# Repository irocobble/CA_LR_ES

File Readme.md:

# Acoustic Sensing Node

**Team:** Aninda Majumdar ([@irocobble](https://github.com/irocobble)) · Subham Basak · Kartik Kajra

A **two-board, field-deployable acoustic sensor** for search-and-rescue. The node
is placed in rubble or debris and listens for signs of a trapped person (voice,
tapping, banging). It works out **which direction** the sound came from and
sends a GPS-tagged alert over LoRa to a rescue dashboard.

Searching collapsed structures is a race against time, and the hardest question
is *where to dig*. Instead of sending people onto unstable rubble to listen, the
node sends the ears in first.

<p align="center">
  
  &nbsp;
  
  <br>
  <em>Left: Board 1, the 8-mic array (2-layer, Ø100 mm). Right: Board 2, the main board (4-layer, 50 × 75 mm).</em>
</p>

---

## Contents

1. [How it works](#how-it-works)
2. [Architecture](#architecture)
3. [Why two boards](#why-two-boards)
4. [Hardware](#hardware)
5. [Microphone array](#microphone-array)
6. [Board-to-board interface](#board-to-board-interface)
7. [Power](#power)
8. [Signal processing on the K210](#signal-processing-on-the-k210)
9. [Voice detection model](#voice-detection-model)
10. [Host software and dashboard](#host-software-and-dashboard)
11. [Prototype results](#prototype-results)
12. [Project status](#project-status)
13. [Open items](#open-items)
14. [Repository layout](#repository-layout)
15. [Getting started](#getting-started)
16. [Engineering notes](#engineering-notes)
17. [Roadmap](#roadmap)
18. [References](#references)

---

## How it works

```
 sound ──▶ 8 MEMS mics ──▶ K210 ──────────────────────────▶ ESP32 ──▶ LoRa ──▶ rescue dashboard
                           │ 1. capture all channels,          │ adds GPS position,
                           │    sampled on the same clock      │ IMU data, timestamp
                           │ 2. "is this a human voice?"       │
                           │ 3. "which direction?"             │
                           └─ sends only the result ───────────┘
                              (angle, confidence, voice yes/no)
```

1. **Listen.** Eight digital microphones sit on a 90 mm circle. They all run
   off one shared clock, so the tiny arrival-time differences between them are
   real and measurable.
2. **Decide.** A small voice-detection model running on the K210 decides
   continuously whether the sound looks like a human voice.
3. **Locate.** The K210 compares the signals from opposite microphones
   (GCC-PHAT) to find the arrival-time difference, then turns it into a bearing.
4. **Report.** Only the result (angle, confidence, level, voice flag) goes to the
   ESP32. No raw audio crosses between the boards.

The K210 stays **powered and listening all the time**. It is not duty-cycled.

---

## Architecture

The system is split across **two boards** that solder together along an 11-pin
castellated edge.

| Board | Layers | Size | Carries |
|---|---|---|---|
| **Board 1: Mic array** | 2 | Ø100 mm | 8× INMP441, Kendryte K210 (Sipeed M1), 12 V→5 V and 12 V→3V3 regulators |
| **Board 2: Main** | 4 | 50 × 75 mm | ESP32 (QFN-48), SX1262 LoRa, MAX-M10S GNSS, MPU-9250 IMU, USB-C hub + 2× USB-UART, 12 V→3V3 regulator |

| Processor | Role |
|---|---|
| **Kendryte K210** (Sipeed M1) | Everything acoustic: I2S master for the array, voice detection, direction finding |
| **ESP32** (QFN-48, 5 × 5 mm) | System host: LoRa, GNSS, IMU, USB, alert formatting |

**Why the K210?** A single K210 I2S peripheral has **four data inputs driven by
one clock generator**. With two microphones per data line, that is eight
channels sampled on exactly the same clock edges. Direction finding depends
entirely on that, and the K210 provides it with nothing to synchronise. It also
has a hardware FFT unit and an audio processor (APU) that can do beamforming,
which we plan to evaluate later.

```
                 ┌──────────────────────────────────────────┐
                 │  BOARD 1: Mic array  (2-layer, Ø100 mm)  │
   8× INMP441 ───┤                                          │
   circle,       │  I2S: 4 data lines, 1 shared clock       │
   r = 45 mm     │            ↓                             │
                 │  K210 / Sipeed M1  (always on)           │
                 │   · voice detection (3-feature model)    │
                 │   · direction of arrival (GCC-PHAT)      │
                 └───────────────┬──────────────────────────┘
                                 │  11-pin castellated edge
                                 │  12 V · mic clock · 2× UART · boot/reset
                 ┌───────────────┴──────────────────────────┐
                 │  BOARD 2: Main  (4-layer, 50 × 75 mm)    │
                 │  ESP32 ── SX1262 LoRa      → U.FL        │
                 │        ── MAX-M10S GNSS    → U.FL        │
                 │        ── MPU-9250 IMU                   │
                 │        ── Wi-Fi/BLE        → U.FL        │
                 │  USB-C → CH334F hub → 2× CP2102N         │
                 └──────────────────────────────────────────┘
```

The IMU is there on purpose. Tapping on rubble produces both a sound and a
vibration. Requiring both reduces false alarms in a way an acoustic-only system
cannot.

---

## Why two boards

The two halves of the design have **opposite needs**:

| | Mic array | Main electronics |
|---|---|---|
| What sets the size | **Physics**: the mics must be far apart to measure direction | **Density**: as small as routing allows |
| Area | Ø100 mm (≈ 7,850 mm²) | 50 × 75 mm (3,750 mm²) |
| Signals | Slow I2S lines, no RF | 3 RF paths, USB, fine-pitch parts |
| Layers needed | **2** | **4** |

On a single board, the whole area would have to be 4-layer, because the LoRa,
GNSS and Wi-Fi antenna feeds need a solid ground plane and 50 Ω traces. We
would be paying 4-layer prices for a large area whose only job is holding
microphones 45 mm from the centre.

### Real cost (as ordered)

Both boards were ordered from **Robu.in**. Prices include shipping.

| Board | Layers | Area | Price paid | Price per mm² |
|---|---|---|---|---|
| Board 1: Mic array | 2 | ≈ 7,850 mm² | **₹900** | ≈ ₹0.115 |
| Board 2: Main | 4 | 3,750 mm² | **₹1,800** | ≈ ₹0.48 |
| **Total (split design)** | | | **₹2,700** | |

On our order, **4-layer cost ≈ 4.2× more per mm² than 2-layer.**

What a single 4-layer board would have cost, at the same ₹0.48/mm²:

| Single-board option | Area | Estimated price | Saving from splitting |
|---|---|---|---|
| Ø100 mm round (smallest that holds the array) | ≈ 7,850 mm² | ≈ ₹3,770 | ≈ 28% |
| 100 × 100 mm (more realistic once both boards' parts fit) | 10,000 mm² | ≈ ₹4,800 | ≈ 44% |

**The split saves roughly 28–44% on bare PCBs.** This is an estimate: fabs have
minimum charges and quantity tiers, so price is not exactly proportional to area.
It is still a fair comparison because both quotes came from the same supplier.

Benefits that do not show up on the invoice:

- **Cheap iteration.** The array geometry is the least certain part of the
  design. Changing it means a new 2-layer board, not a new 4-layer one.
- **Contained failure.** A damaged mic board does not scrap the main board.
- **Assembly yield.** The finest-pitch parts (ESP32 QFN-48 at 0.35 mm,
  2× QFN-28, QFN-24) are all on the small board.
- **RF kept away from audio.** The three antennas are physically separated from
  the microphone traces.

**The trade-off:** the castellated joint is a new failure point and cannot be
probed once soldered. That is why only slow signals cross it: no RF, no
high-speed bus.

---

## Hardware

### Board 1: Mic array (`Board1_2layers/Mic+MPU/`)

| Function | Device | Ref |
|---|---|---|
| Acoustic processor | Sipeed M1 (Kendryte K210) | U12 |
| Microphones | 8× INMP441 I2S MEMS | U1–U6, U15, U16 |
| Buck 12 V → 5 V (K210) | AP63205WU | U14 |
| Buck 12 V → 3V3 (mics) | AP63203WU | U10 |
| Power input | JST-XH 2-pin, polarised | J1 |
| Board interface | 11-pin castellated, 3.2 mm pitch | J3 |
| Buttons | Boot, Reset | SW4, SW3 |

> The `Mic+MPU` folder name is historical. The MPU-9250 is on Board 2.

<p align="center">
  
  &nbsp;
  
  <br><em>Board 1, top and bottom. The microphone sound holes are on the bottom face.</em>
</p>

<p align="center">
  
  <br><em>Board 1 layout in KiCad.</em>
</p>

### Board 2: Main (`board2_4layers/`)

| Function | Device | Ref |
|---|---|---|
| Host MCU | ESP32 (QFN-48, 5 × 5 mm) | U7 |
| External SPI flash | SPI NOR, SOIC-8 | U6 |
| LoRa transceiver | SX1262 module | U1 |
| GNSS receiver | u-blox MAX-M10S | U3 |
| IMU | MPU-9250 (9-axis) | U4 |
| USB hub | CH334F | CH334F1 |
| USB-UART bridges (ESP32 + K210) | 2× CP2102N | U8, U9 |
| USB ESD protection | USBLC6-4SC6 | U2 |
| Buck 12 V → 3V3 | AP63203WU | U5 |
| Antennas | 3× U.FL: LoRa, GNSS, Wi-Fi | J2, J4, J5 |
| USB connector | USB Type-C | J1 |
| Crystals | 40 MHz (ESP32), 12 MHz (hub) | Y2, Y1 |
| Buttons | EN, BOOT | SW1, SW2 |

Stack-up: GND on F.Cu, In1.Cu and B.Cu; +3V3 on In2.Cu.

<p align="center">
  
  &nbsp;
  
  <br><em>Board 2, top and bottom.</em>
</p>

<p align="center">
  
  <br><em>Board 2 layout in KiCad.</em>
</p>

---

## Microphone array

Eight INMP441 digital microphones on a circle of **radius 45.00 mm**, spaced
45° apart. Each one is rotated to face the centre, so every microphone has the
same trace shape back to the K210.

Two microphones share each data line. The INMP441's `L/R` pin decides which
half of the stereo frame each one uses: one takes the left slot, the other the
right.

| Data line | K210 pin | Mics | Angles |
|---|---|---|---|
| `SD_1` | IO20 | U1, U2 | 90°, 45° |
| `SD_2` | IO21 | U5, U6 | 0°, 315° |
| `SD_3` | IO22 | U15, U16 | 270°, 225° |
| `SD_4` | IO23 | U3, U4 | 180°, 135° |
| `SCK_MIC` | IO18 | shared bit clock | |
| `WS` | IO19 | shared word select | |

All eight sample on the same bit clock, so every channel is **phase-coherent**.
This is exactly what direction finding needs, and it is why digital MEMS mics
were chosen over analog mics behind a multiplexed ADC.

Every K210 IO used has a **200 Ω series resistor and an ESD diode**, as Sipeed
requires for the M1 module.

> **Sound enters from the bottom.** Each mic sits over a 1.05 mm hole through
> the PCB, so the openings in the enclosure must be on the bottom face.

**Geometry numbers:**

| Quantity | Value | Why it matters |
|---|---|---|
| Adjacent mic spacing | 2r·sin(22.5°) = 34.4 mm | Spatial aliasing above c / (2 × 0.0344) ≈ **5.0 kHz** |
| Opposite mic spacing | 90 mm | Longest baseline, best angle resolution |
| Max arrival-time difference | 90 mm / 343 m/s ≈ 262 µs | Only ≈ **4.2 samples** at 16 kHz, so sub-sample timing is required |

> **About IO20.** On the Sipeed **Maix development board**, IO20 is wired to the
> board's own onboard microphone, so it cannot be used for an external mic there.
> On our PCB the bare **M1 module** is used, which has no onboard microphone, so
> IO20 is free. This only matters if you test the firmware on a Maix board.

---

## Board-to-board interface

11 positions, 3.2 mm pitch, castellated. Board 2 solders directly onto Board 1,
with no connector and no cable.

| Pin | Net | Direction | Purpose |
|---|---|---|---|
| 1 | `+12V` | → Board 2 | Unregulated; each board regulates locally |
| 2 | `SCK_MIC` | K210 → ESP32 | Mic bit clock |
| 3 | `WS` | K210 → ESP32 | Mic word select |
| 4 | `SD1` | mics → ESP32 | Lets the ESP32 hear one mic pair (spare / diagnostics) |
| 5 | `UART_TX` | ESP32 → K210 | Commands |
| 6 | `UART_RX` | K210 → ESP32 | Results: voice flag, confidence, bearing |
| 7 | `RX` | K210 → CP2102N | K210 programming, transmit |
| 8 | `TX` | CP2102N → K210 | K210 programming, receive |
| 9 | `Boot` | CP2102N → K210 | IO16 boot-mode select |
| 10 | `RST` | CP2102N → K210 | Reset (1.8 V domain) |
| 11 | `GND` | | Return |

`TX` and `RX` on pins 7–8 are named **from the USB bridge's point of view** on
both boards.

Pins 2–4 were originally intended for a low-power wake detector on the ESP32.
Since the K210 now stays on all the time, that wake path is not needed. The
pins stay as a spare way for the ESP32 to listen to one mic pair. If used, the
ESP32 must be an I2S **slave**, because the K210 drives the clock.

**No raw audio crosses the joint in normal operation.** The mics feed the K210
directly; the UART carries only results.

---

## Power

```
12 V in (JST-XH, polarised)
   │
   ├── Board 1 ── AP63205 ──▶ +5V   → Sipeed M1 (K210)
   │           └─ AP63203 ──▶ +3V3  → 8× INMP441
   │
   └── via J3 pin 1 ──▶ Board 2 ── AP63203 ──▶ +3V3
                                     → ESP32, SX1262, MAX-M10S, MPU-9250, flash
```

Only 12 V and GND cross the joint, so no regulated rail loses voltage across it
and the RF and audio sections do not share regulator noise.

**Estimated ≈ 3.3 W total (≈ 320 mA at 12 V)**, mostly the K210 (≈ 1.5 W).
This is an estimate and will be measured once the boards are assembled.

---

## Signal processing on the K210

The firmware is plain C on the **kendryte-standalone-sdk**, in two CMake projects:

| Project | Build flag | Output | Use |
|---|---|---|---|
| Recorder | `-DPROJ=Recorder` | `Recorder.bin` | Streams raw mic audio to the PC for datasets and calibration |
| Detector | `-DPROJ=Detector` | `Detector.bin` | Runs voice detection and direction finding on the chip |

### Capture

- 16 kHz nominal. The K210's PLL gives a real rate of about **15,986 Hz**. The
  difference is small and does not affect the results.
- Samples are 32-bit from the INMP441, shifted down to 16-bit
  (`SAMPLE_SHIFT = 13`, the smallest shift where no channel clips).
- The conversion to 16-bit **saturates** instead of wrapping. A wrapped sample
  looks like a loose wire, which is very confusing during debugging.
- A **100 Hz high-pass filter** (4th-order Butterworth) removes rumble and DC
  before anything else.

### Direction of arrival (GCC-PHAT)

For each pair of opposite microphones:

1. Take a **1024-point FFT (64 ms)** of both channels.
2. Compute the cross-spectrum and divide each bin by its own magnitude
   (the **PHAT** weighting). This keeps only phase, which is what carries timing.
3. **Keep only 300–3400 Hz** (the speech band). Without this mask, the empty
   bins are amplified to the same weight as real ones and the answer is
   essentially random. Measured: a true delay of 1.50 samples was estimated as
   0.14 unmasked and 1.49 masked.
4. **Search for the delay directly at fractional lags.** A coarse pass in
   0.10-sample steps, then a fine pass in 0.01-sample steps around the best one.
   Each lag is evaluated with the FFT shift theorem, so no curve-fitting is
   needed. This matters because the whole array spans only about 4 samples of
   delay; whole-sample steps would give very coarse bearings.
5. The search range comes from the spacing:
   `max lag = spacing / c × fs × 1.4` (40% extra for echoes and measurement error).
6. Two perpendicular pairs give `lag_x` and `lag_y`, and the bearing is
   `atan2(lag_y, lag_x)`.
7. Results are rejected if the sound is too quiet (`-45 dB` level gate), the
   correlation is too weak (`< 0.08`), or the delay is impossibly large.

Direction finding runs on **any loud enough sound**, not only on speech. The
voice flag is reported alongside it.

**Calibration matters.** On the prototype, two I2S channels start on different
word-select edges, which adds a constant offset between them. We measured
`lag_x` bias = **−0.93** and `lag_y` bias = **+0.95** samples, and the firmware
subtracts them (`DOA_LAG_X_BIAS`, `DOA_LAG_Y_BIAS`).

### What the array can and cannot do

- It reports **one bearing per update**: the dominant sound source. Separating
  several people talking at once needs a much larger array (roughly 0.5 m or
  more across), which is not practical for a node this size.
- It gives **direction, not distance**. On the dashboard, how far a dot is from
  the centre shows **how old** the detection is, not how far away the source is.
- Distance comes from **combining several nodes** (triangulation), which is on
  the roadmap.

### Result packet (K210 → host)

20 bytes, sent at `REPORT_HZ = 20`:

```
[5A A6] [len=0x10] [seq] [angle×10 : i16] [conf×1000 : u16] [score×100 : i16]
[level_db×10 : i16] [speech : u8] [warm : u8] [lag_x×100 : i16] [lag_y×100 : i16] [xor] [pad]
```

Raw-audio frames from the Recorder use:

```
[5A A5] [seq : u8] [blk : u16] [nch : u8] [int16 samples × blk·nch] [sum16]
```

The sequence number lets the PC detect and count dropped bytes. Before framing,
one lost byte silently turned the rest of a recording into noise while the WAV
file still looked valid.

---

## Voice detection model

A **logistic regression on 3 hand-picked features**, small enough to run on the
K210 as a single dot product.

| Feature | What it measures |
|---|---|
| `harmonicity` | Strength of the pitch peak in the autocorrelation (human pitch range, lags 40–266 samples) |
| `voice_band_ratio` | Share of energy in 300–3400 Hz (512-point Hann-window FFTs) |
| `snr_db` | Level above a rolling noise floor (20th percentile over the last 8 s) |

- Trained in Python (`Accoustic_Sensing_Node/ML/`). The feature scaler is folded into the weights and
  exported as `vad3_model.h`, so the chip does no extra scaling.
- Decision threshold (logit) **2.389**, then smoothed over **3** consecutive
  decisions (`VAD_SMOOTH_K = 3`).
- `FEATURE_VERSION = 4`. The firmware and Python feature code must match. The
  version number makes a mismatch obvious.
- Evaluation uses **grouped cross-validation by recording file**, so clips from
  the same recording never appear in both training and test. The main metric is
  **recall at 5% false-positive rate**, because false alarms are what make
  rescuers stop trusting a sensor.

### Dataset status

Our own recordings (`INMP_441_Dataset/`) are combined with public datasets
(`Public_Dataset/`). Every file goes through a quality check (dropped bytes,
clipping, DC offset, rumble, SNR) before it is used.

We also run a **confound check**: a classifier trained only on the *background*
of each recording, with the speech removed. If it can still tell the classes
apart, the model could be learning *which session* a clip came from instead of
*whether someone is speaking*.

| Dataset version | Background-only AUC | Target |
|---|---|---|
| First dataset | 0.905 – 0.94 | < 0.65 |
| Latest | **0.812** | < 0.65 |

It is improving, but still above target. Recording speech and non-speech
**interleaved in the same session, room and distance** is the fix in progress.

---

## Host software and dashboard

Python tools on the PC, all reachable from one entry point:

```
python capstone.py --help
```

| Command | What it does |
|---|---|
| `status`, `devices`, `linktest`, `inspect` | Check setup, list serial ports, test the link, inspect captures |
| `record` | Record labelled clips from the board |
| `qc`, `filters` | Dataset quality check, filter tests |
| `train`, `train-corpus`, `export` | Train the model and export `vad3_model.h` |
| `predict` | Run the model on WAV files |
| `serve`, `monitor`, `gui` | Live API + dashboard, console monitor, desktop GUI (`sar_gui.py`) |

**API server** (`api_server.py`): reads the K210's result packets from serial
and serves them over HTTP on all interfaces (port 8000 by default), so a phone
on the same Wi-Fi hotspot can open the dashboard.

| Endpoint | Returns |
|---|---|
| `/api/detections` | Detections from the last 15 s |
| `/api/state` | Latest bearing, level, voice flag |
| `/api/threshold` | Read or change the detection threshold |
| `/api/health` | Server and serial-link status |
| `/` | `dashboard.html`, the radial display |

It uses a threaded server with HTTP/1.1 keep-alive, which fixed the lag we saw
on phones over a hotspot.

<p align="center">
  
  <br><em>Live dashboard in the browser.</em>
</p>

---

## Prototype results

Before the PCBs, the full pipeline was built on a breadboard: a Sipeed Maix
board with **4 INMP441 mics in a 40 mm square**. Opposite corners are paired, so
the baseline is the square's diagonal, **56.6 mm**.

<!-- Add the photo later: save it as Accoustic_Sensing_Node/images/prototype_breadboard.jpg and delete these comment markers
<p align="center">
  
  <br><em>Breadboard prototype: Maix board + 4 INMP441 in a 40 mm square.</em>
</p>
-->

What works on the prototype:

- Phase-coherent 4-channel capture on one I2S peripheral
- On-chip voice detection and GCC-PHAT bearing, streamed live to the dashboard
- North and West bearings accurate before calibration; East and South were
  tilted until the cross-channel bias correction was added

**A measured accuracy table (true angle vs reported angle, several distances)
will be added once the PCB is assembled.** Numbers from the breadboard are not
representative of the final board, so they are not published here.

---

## Project status

### Hardware

- [x] Board 1 schematic and layout complete; 8 mics at exact geometry (r = 45.000 mm)
- [x] Board 1: K210 power, programming, boot/reset, 1.8 V reset domain; 200 Ω + ESD on every IO
- [x] Board 2 schematic and layout complete, DRC clean
- [x] Board 2: ESP32 core, LoRa, GNSS (active-antenna bias-T), IMU, USB-C hub with auto boot/reset for both processors
- [x] **Both boards ordered** (Robu.in)
- [ ] Assembly and bring-up
- [ ] Measured power consumption

### Firmware (K210)

- [x] `Recorder` and `Detector` CMake projects
- [x] Framed, checksummed audio stream with sequence numbers
- [x] On-chip 3-feature voice detector (`vad3_model.h`, `FEATURE_VERSION = 4`)
- [x] Working 4-mic GCC-PHAT direction finding on the prototype, with bias calibration
- [ ] 8-channel capture on the new array
- [ ] Re-measure all DOA constants on the circular array
- [ ] Evaluate the K210 APU hardware beamformer

### Firmware (ESP32)

- [ ] LoRa, GNSS and IMU drivers
- [ ] UART link to the K210 and alert formatting
- [ ] Sound + vibration fusion

### Host software

- [x] `capstone.py` single entry point, `sar_gui.py` desktop GUI
- [x] API server + dashboard, 15 s detection window, keep-alive
- [x] Dataset QC, training, grouped evaluation, C-header export
- [ ] Multi-node triangulation view

---

## Open items

| # | Item | Where | What to do |
|---|---|---|---|
| 1 | **DOA constants are for the 4-mic breadboard** | Firmware | `DOA_SPACING_MM`, `SAMPLE_SHIFT` and both lag biases must be re-measured on the circular array (opposite pair = 90 mm) |
| 2 | **Every opposite pair spans two data lines** | Firmware | e.g. 0° is on `SD_2` and 180° on `SD_4`. Each data line may have its own timing offset, so calibrate a **per-data-line offset** at bring-up (the prototype needed ≈ ±0.9 samples) |
| 3 | **Channel order is not ring order** | Firmware | K210 inputs D0–D3 = `SD_4`, `SD_3`, `SD_2`, `SD_1`. Build the channel→angle table and confirm it with a tap test at each mic |
| 4 | Dataset confound | ML | Background-only AUC 0.812, target < 0.65. Record both classes interleaved in the same session |
| 5 | Measured DOA accuracy table | Testing | After PCB assembly |
| 6 | Flash part name | Board 2 | U6 value field shows `AT25SF081`; update it to the part actually fitted |
| 7 | CP2102N no-connect pins | Board 2 | Add no-connect flags on U8/U9 pin 10 (cosmetic, clean ERC) |
| 8 | Stale BOM export | Board 2 | `Accoustic_Sensing_Node.csv` is from an older revision; re-export from KiCad |
| 9 | Battery operation | Both | Node runs from 12 V only; battery + boost planned |
| 10 | One M2.5 mounting hole per board | Both | Add more before the enclosure is fixed |
| 11 | Enclosure | Mechanical | Sound openings on the bottom face, antenna clearance, survives drops |

---

## Repository layout

Everything for the acoustic node lives in the `Accoustic_Sensing_Node/` folder:

```text
Accoustic_Sensing_Node/
├── README.md                     ← copy of this file
├── images/                       ← all pictures used in this README
│
├── Board1_2layers/
│   ├── Mic+MPU/                  KiCad project: mic array board (2-layer)
│   │   ├── Mic.pretty/           INMP441 footprint (with sound hole)
│   │   ├── Connectors.pretty/    11-pin castellated footprint
│   │   └── output/               Gerbers as ordered
│   └── mic/INMP441.kicad_mod
│
├── board2_4layers/               KiCad project: main board (4-layer)
│   ├── *.pretty/                 custom footprints (LoRa, GNSS, USB hub, edge pads)
│   └── Output/                   Gerbers + drill as ordered
│
├── Recording_Via_IOT_Devices/
│   ├── firmware/
│   │   ├── K210/src/Recorder/    raw multi-channel streaming
│   │   ├── K210/src/Detector/    main_detector.c, sar_features.c, sar_doa.c, vad3_model.h
│   │   └── esp32_1mic/           single-mic ESP32 recorder (dataset collection)
│   ├── record.py, devices.py     recorder and per-board serial settings
│   ├── api_server.py             HTTP API + serial reader
│   ├── dashboard.html            radial live display
│   ├── detector_monitor.py       console monitor
│   └── link_test.py              serial link test
│
├── ML/                           features, training, QC, export to C header
├── capstone.py                   single entry point for all tools
├── sar_gui.py                    desktop GUI
├── requirements.txt
├── run_gui.bat, build_exe.bat
└── BUILD.md                      building the firmware and the .exe
```

Datasets (`INMP_441_Dataset/`, `Public_Dataset/`) are **not** stored in the repo
because of their size.

---

## Getting started

Run everything from inside the acoustic folder:

```bash
cd Accoustic_Sensing_Node
```

### 1. Python tools

```bash
pip install -r requirements.txt
python capstone.py status
```

Try the dashboard with no hardware:

```bash
python Recording_Via_IOT_Devices/api_server.py --demo
# open http://localhost:8000
```

### 2. Build and flash the K210 firmware

```bash
cd Recording_Via_IOT_Devices/firmware/K210
mkdir build && cd build
cmake .. -DPROJ=Detector -DTOOLCHAIN=/opt/kendryte-toolchain/bin
make
kflash -p COM12 -b 1500000 Detector.bin
```

> **Delete the `build/` folder when switching between `Recorder` and
> `Detector`.** CMake caches the project name, so otherwise it silently builds
> the old one again.

See `BUILD.md` for Windows details.

### 3. Run live

```bash
python Recording_Via_IOT_Devices/api_server.py --port COM12
# optional: --capture session.bin  (save the raw stream to replay later)
#           --wav heard.wav        (save what the detector is hearing)
#           --replay session.bin   (replay a saved session, no hardware)
```

Then open `http://<pc-ip>:8000` on any device on the same network.

---

## Engineering notes

Things learned the hard way, kept here so they are not learned twice:

- **Measure, don't assume.** Every DOA constant on the prototype came from
  measurement, not a datasheet. Mic spacing is measured between the actual
  sound holes, in **millimetres**.
- **Serial port settings.** pyserial asserts DTR and RTS by default. That
  resets the ESP32 and puts the K210 into its bootloader, where it sends
  nothing. `devices.py` clears both before opening the port.
- **UART pins.** The ESP32 transmits on GPIO5, so the K210 uses **IO31 as RX and
  IO30 as TX**.
- **ESP32 GPIO12 stays unconnected.** It sets the flash voltage at reset; high
  selects 1.8 V.
- **K210 IO voltages.** IO0–IO35 are 3.3 V, IO36–IO47 are 1.8 V. Every signal
  used is IO35 or below.
- **ESP32 flash mode.** Start in DIO; QIO needs chip-specific setup.
- **Faulty mics happen.** During prototyping one INMP441 was dead and one had
  a blocked sound hole (≈ 6.6 dB quieter). Check every channel's level before
  trusting a bearing.

---

## Roadmap

- Assemble both boards; bring up 8-channel capture
- Re-calibrate DOA on the circular array and publish a measured accuracy table
- Compare the K210 APU hardware beamformer with software GCC-PHAT
- Move the voice model to the 8-mic front end
- ESP32: LoRa, GNSS, IMU and the end-to-end alert path
- Combine sound and vibration (IMU) to reduce false alarms
- Multi-node triangulation on the dashboard
- Battery power (the K210 stays always on, so battery size is set by its ≈ 1.5 W)
- Enclosure: sound openings, antenna clearance, drop survival

---

## Applications

**Main use:** search-and-rescue: locating people trapped under collapsed
buildings. Several nodes across a site turn a large, uncertain search area into
a short list of places worth digging.

**Other uses:** perimeter and intrusion detection, wildlife monitoring, noise
source mapping, remote sensor networks with human-presence detection.

---

## References

- C. Knapp and G. Carter, *The Generalized Correlation Method for Estimation of
  Time Delay*, IEEE Trans. ASSP, 1976 (GCC-PHAT)
- J. DiBiase, *A High-Accuracy, Low-Latency Technique for Talker Localization
  in Reverberant Environments Using Microphone Arrays*, PhD thesis, Brown
  University, 2000 (SRP-PHAT)
- Sipeed M1 datasheet: module pinout, IO voltages, reset constraints
- Kendryte K210 datasheet and kendryte-standalone-sdk
- InvenSense INMP441 datasheet
- Espressif *ESP32 Hardware Design Guidelines*

---

## License

Under active development. License to be decided.

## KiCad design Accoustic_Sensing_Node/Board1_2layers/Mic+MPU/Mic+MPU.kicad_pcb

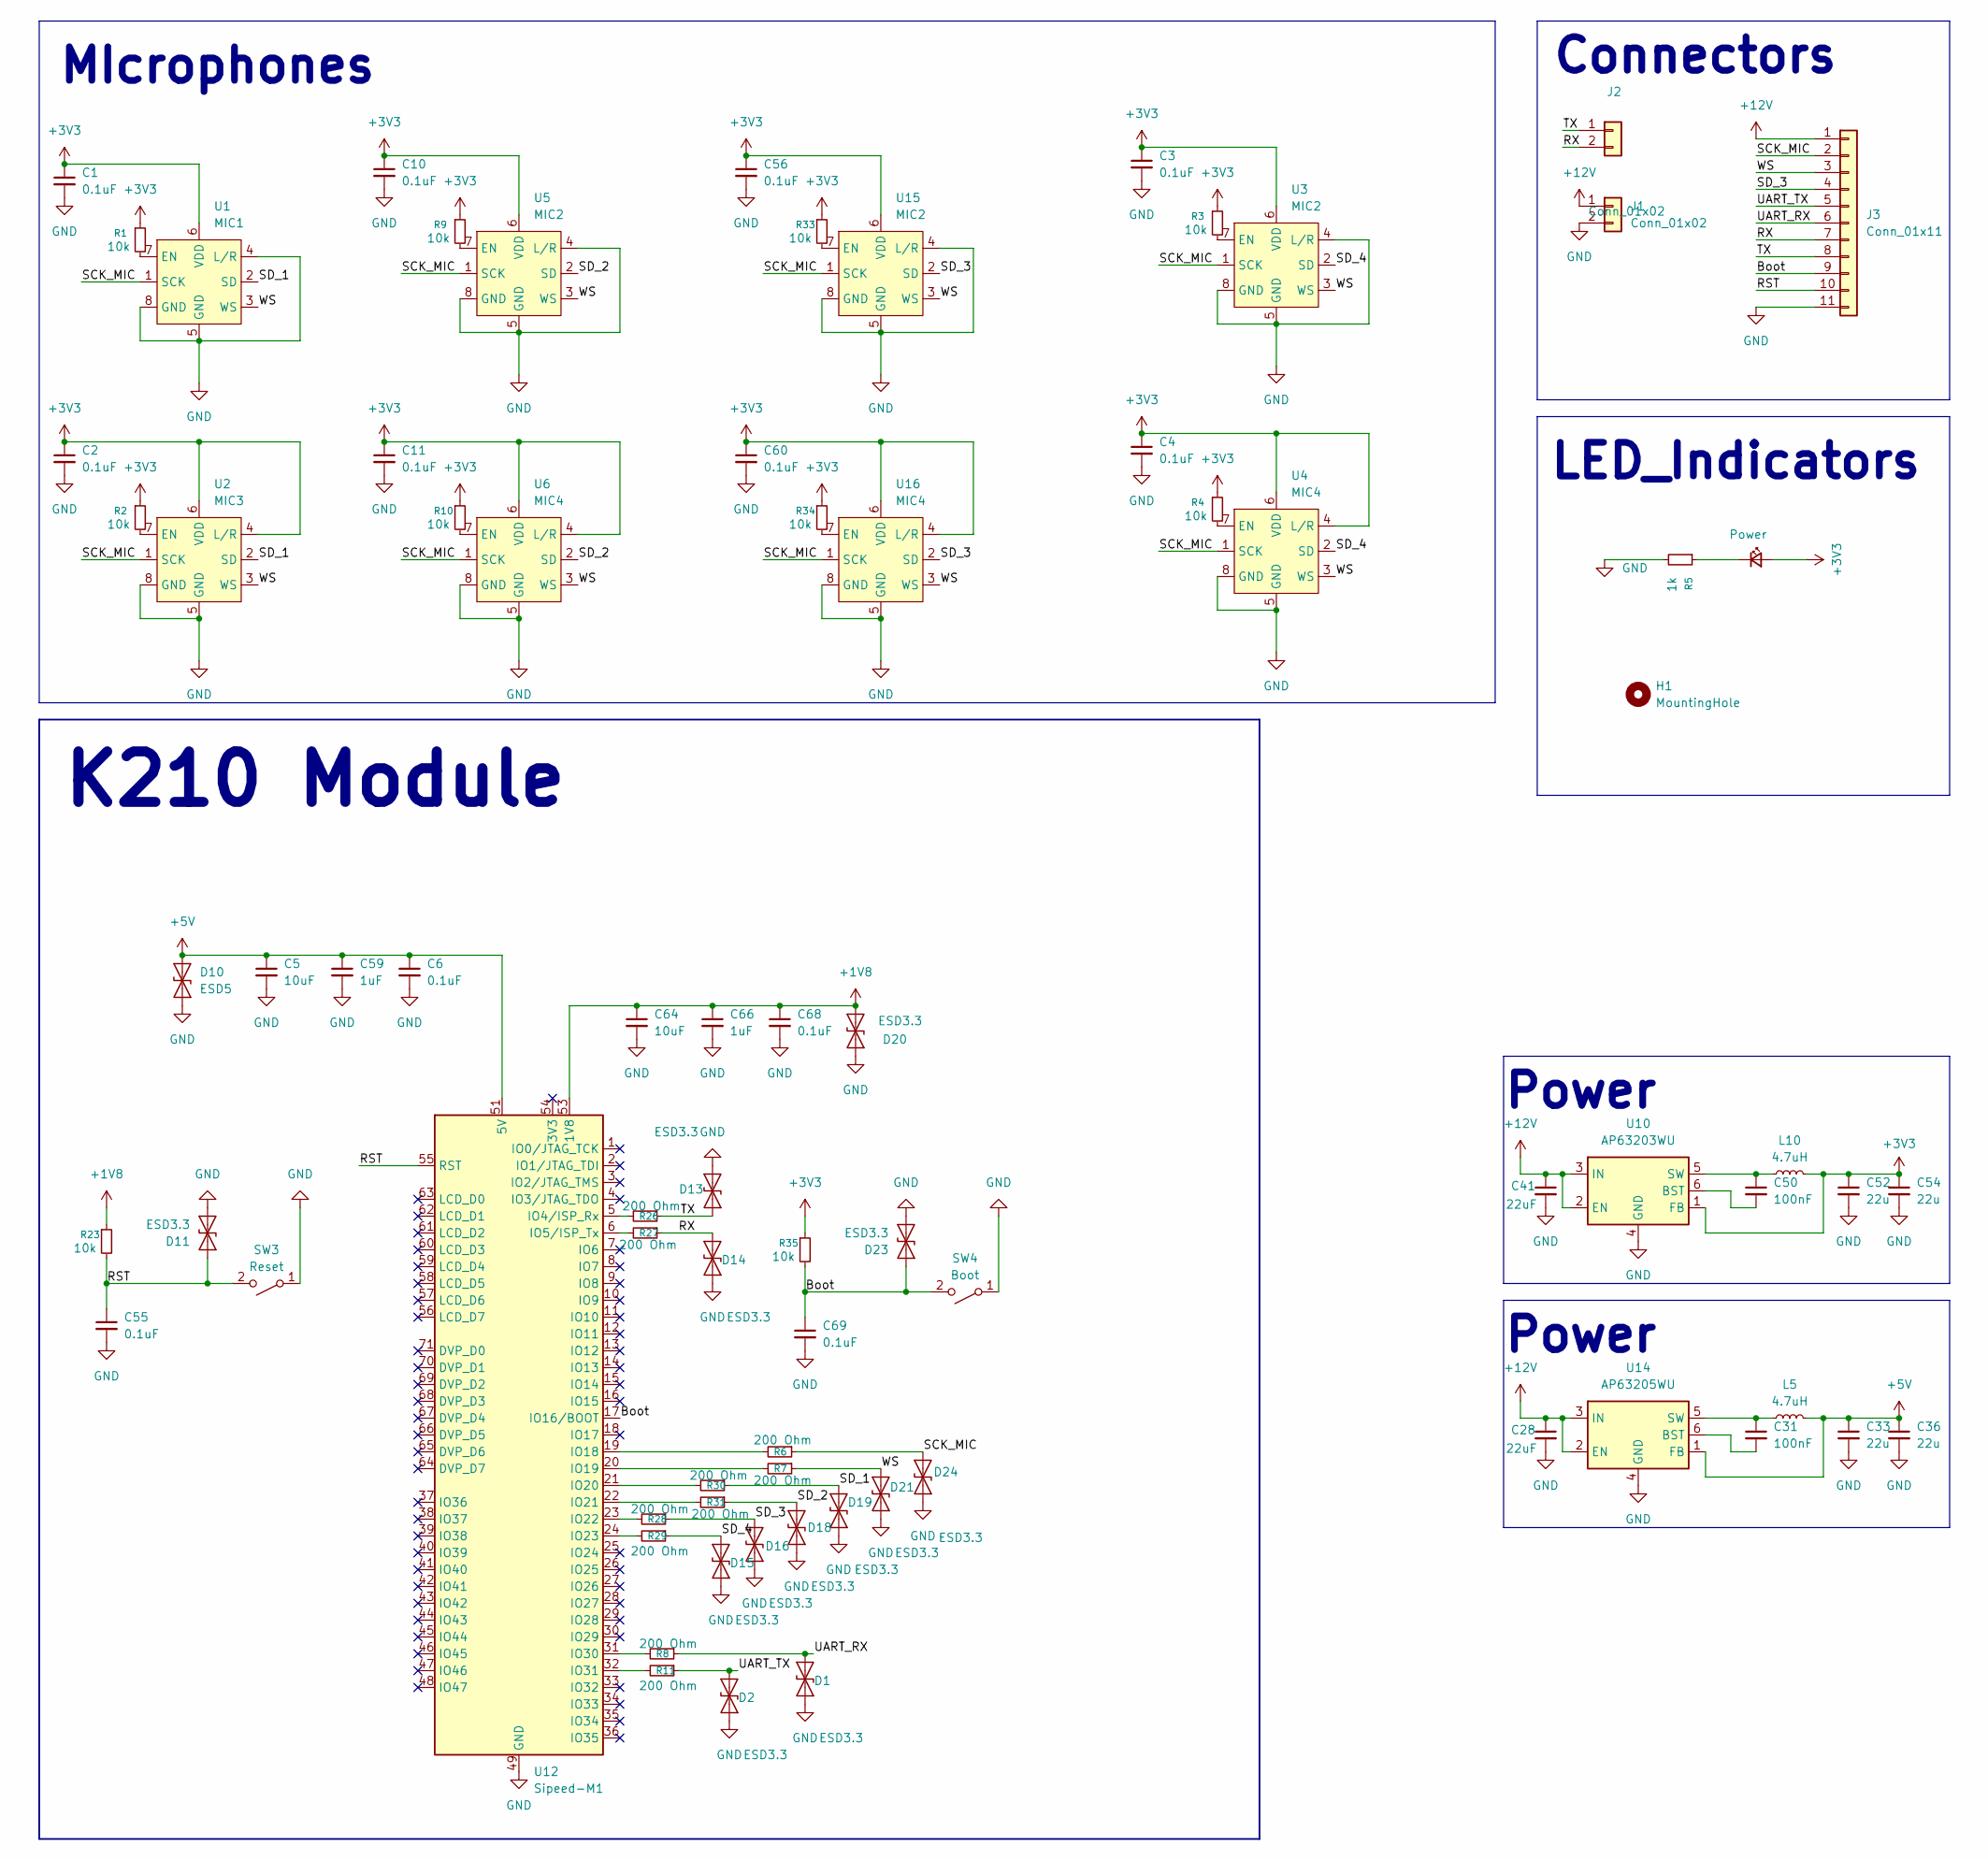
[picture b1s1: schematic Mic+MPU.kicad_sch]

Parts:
C1, C2, C3, C4, C6, C10, C11, C55, C56, C60, C68, C69: 0.1uF; C_0402_1005Metric
C5, C64: 10uF; C_0805_2012Metric
C28, C41: 22uF; C_0805_2012Metric
C31, C50: 100nF; C_0603_1608Metric
C33, C36, C52, C54: 22u; C_0805_2012Metric
C59, C66: 1uF; C_0603_1608Metric
D1, D2, D11, D13, D14, D15, D16, D18, D19, D20, D21, D23, D24: ESD3.3; D_SOD-523
D3: Power; LED_0805_2012Metric
D10: ESD5; D_SOD-523
H1: MountingHole; MountingHole_2.7mm_M2.5_Pad_TopBottom
J1: Conn_01x02; JST_XH_B2B-XH-A_1x02_P2.50mm_Vertical
J2: Conn_01x02; PinHeader_1x02_P2.54mm_Vertical
J3: Conn_01x11; Con_01x011
L5, L10: 4.7uH; L_Sunlord_SWPA6020S
R1, R2, R3, R4, R9, R10, R23, R33, R34, R35: 10k; R_0402_1005Metric
R5: 1k; R_0402_1005Metric
R6, R7, R8, R11, R26, R27, R28, R29, R30, R31: 200 Ohm; R_0402_1005Metric
SW3: Reset; SW_CS1213AGF260_CRS
SW4: Boot; SW_CS1213AGF260_CRS
U1: MIC1; INMP441
U2: MIC3; INMP441
U3, U5, U15: MIC2; INMP441
U4, U6, U16: MIC4; INMP441
U10: AP63203WU; TSOT-23-6
U12: Sipeed-M1
U14: AP63205WU; TSOT-23-6

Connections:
+1V8: C64.1, C66.1, C68.1, D20.1 (A1), R23.1, U12.53 (1V8)
+3V3: C1.1, C2.1, C3.1, C4.1, C10.1, C11.1, C52.1, C54.1, C56.1, C60.1, D3.2 (A), L10.2, R1.1, R2.1, R3.1, R4.1, R9.1, R10.1, R33.1, R34.1, R35.1, U1.6 (VDD), U2.4 (L/R), U2.6 (VDD), U3.6 (VDD), U4.4 (L/R), U4.6 (VDD), U5.6 (VDD), U6.4 (L/R), U6.6 (VDD), U10.1 (FB), U15.6 (VDD), U16.4 (L/R), U16.6 (VDD)
+5V: C5.1, C6.1, C33.1, C36.1, C59.1, D10.2 (A2), L5.2, U12.51 (5V), U12.52 (5V), U14.1 (FB)
+12V: C28.1, C41.1, J1.1, J3.1, U10.2 (EN), U10.3 (IN), U14.2 (EN), U14.3 (IN)
/Boot: C69.1, D23.2 (A2), J3.9, R35.2, SW4.2 (B), U12.17 (IO16/BOOT)
/RST: C55.1, D11.2 (A2), J3.10, R23.2, SW3.2 (B), U12.55 (RST)
/RX: D14.2 (A2), J2.2, J3.7, R27.1
/SCK_MIC: D24.2 (A2), J3.2, R6.1, U1.1 (SCK), U2.1 (SCK), U3.1 (SCK), U4.1 (SCK), U5.1 (SCK), U6.1 (SCK), U15.1 (SCK), U16.1 (SCK)
/SD_1: D19.2 (A2), R30.1, U1.2 (SD), U2.2 (SD)
/SD_2: D18.2 (A2), R31.1, U5.2 (SD), U6.2 (SD)
/SD_3: D16.2 (A2), J3.4, R28.1, U15.2 (SD), U16.2 (SD)
/SD_4: D15.2 (A2), R29.1, U3.2 (SD), U4.2 (SD)
/TX: D13.2 (A2), J2.1, J3.8, R26.1
/UART_RX: D1.2 (A2), J3.6, R8.1
/UART_TX: D2.2 (A2), J3.5, R11.1
/WS: D21.2 (A2), J3.3, R7.1, U1.3 (WS), U2.3 (WS), U3.3 (WS), U4.3 (WS), U5.3 (WS), U6.3 (WS), U15.3 (WS), U16.3 (WS)
GND: C1.2, C2.2, C3.2, C4.2, C5.2, C6.2, C10.2, C11.2, C28.2, C33.2, C36.2, C41.2, C52.2, C54.2, C55.2, C56.2, C59.2, C60.2, C64.2, C66.2, C68.2, C69.2, D1.1 (A1), D2.1 (A1), D10.1 (A1), D11.1 (A1), D13.1 (A1), D14.1 (A1), D15.1 (A1), D16.1 (A1), D18.1 (A1), D19.1 (A1), D20.2 (A2), D21.1 (A1), D23.1 (A1), D24.1 (A1), J1.2, J3.11, R5.2, SW3.1 (A), SW4.1 (A), U1.4 (L/R), U1.5 (GND), U1.8 (GND), U2.5 (GND), U2.8 (GND), U3.4 (L/R), U3.5 (GND), U3.8 (GND), U4.5 (GND), U4.8 (GND), U5.4 (L/R), U5.5 (GND), U5.8 (GND), U6.5 (GND), U6.8 (GND), U10.4 (GND), U12.49 (GND), U12.50 (GND), U12.72 (GND), U14.4 (GND), U15.4 (L/R), U15.5 (GND), U15.8 (GND), U16.5 (GND), U16.8 (GND)
unnamed: D3.1 (K), R5.1
unnamed: R1.2, U1.7 (EN)
unnamed: R2.2, U2.7 (EN)
unnamed: R3.2, U3.7 (EN)
unnamed: R4.2, U4.7 (EN)
unnamed: R9.2, U5.7 (EN)
unnamed: R10.2, U6.7 (EN)
unnamed: C50.2, U10.6 (BST)
unnamed: C50.1, L10.1, U10.5 (SW)
unnamed: R26.2, U12.5 (IO4/ISP_Rx)
unnamed: R27.2, U12.6 (IO5/ISP_Tx)
unnamed: R6.2, U12.19 (IO18)
unnamed: R7.2, U12.20 (IO19)
unnamed: R30.2, U12.21 (IO20)
unnamed: R31.2, U12.22 (IO21)
unnamed: R28.2, U12.23 (IO22)
unnamed: R29.2, U12.24 (IO23)
unnamed: R8.2, U12.31 (IO30)
unnamed: R11.2, U12.32 (IO31)
unnamed: C31.2, U14.6 (BST)
unnamed: C31.1, L5.1, U14.5 (SW)
unnamed: R33.2, U15.7 (EN)
unnamed: R34.2, U16.7 (EN)

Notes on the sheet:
K210 Module
Power
Connectors
LED_Indicators
MIcrophones

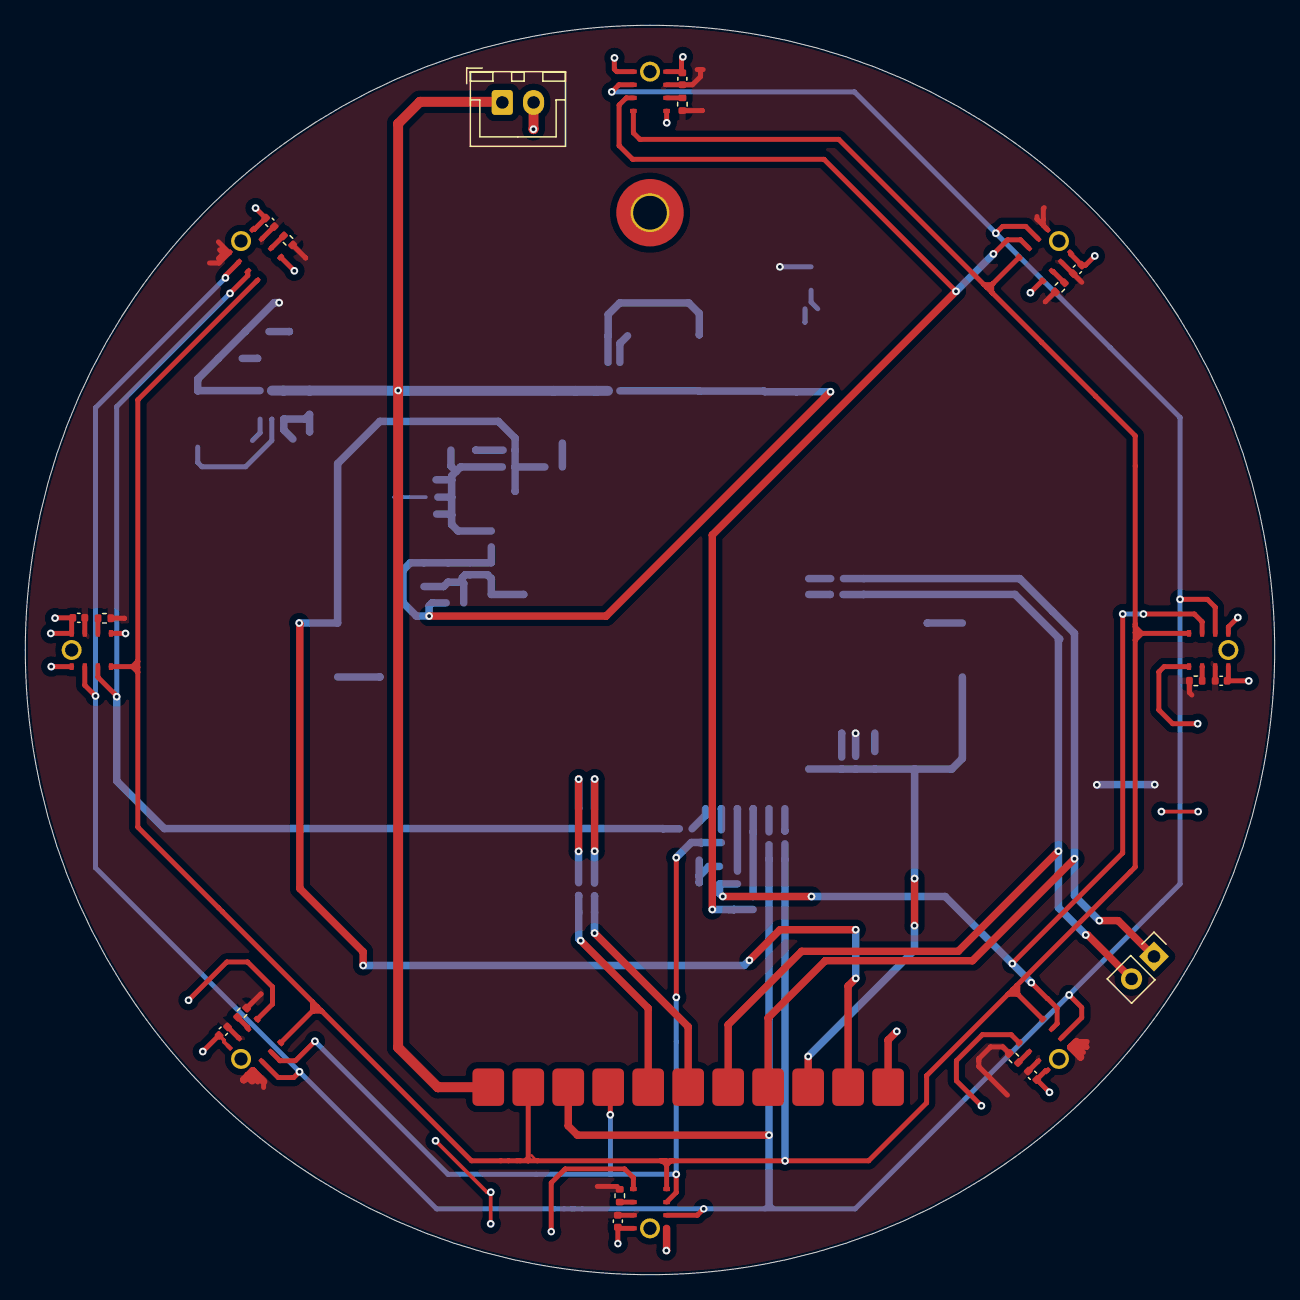
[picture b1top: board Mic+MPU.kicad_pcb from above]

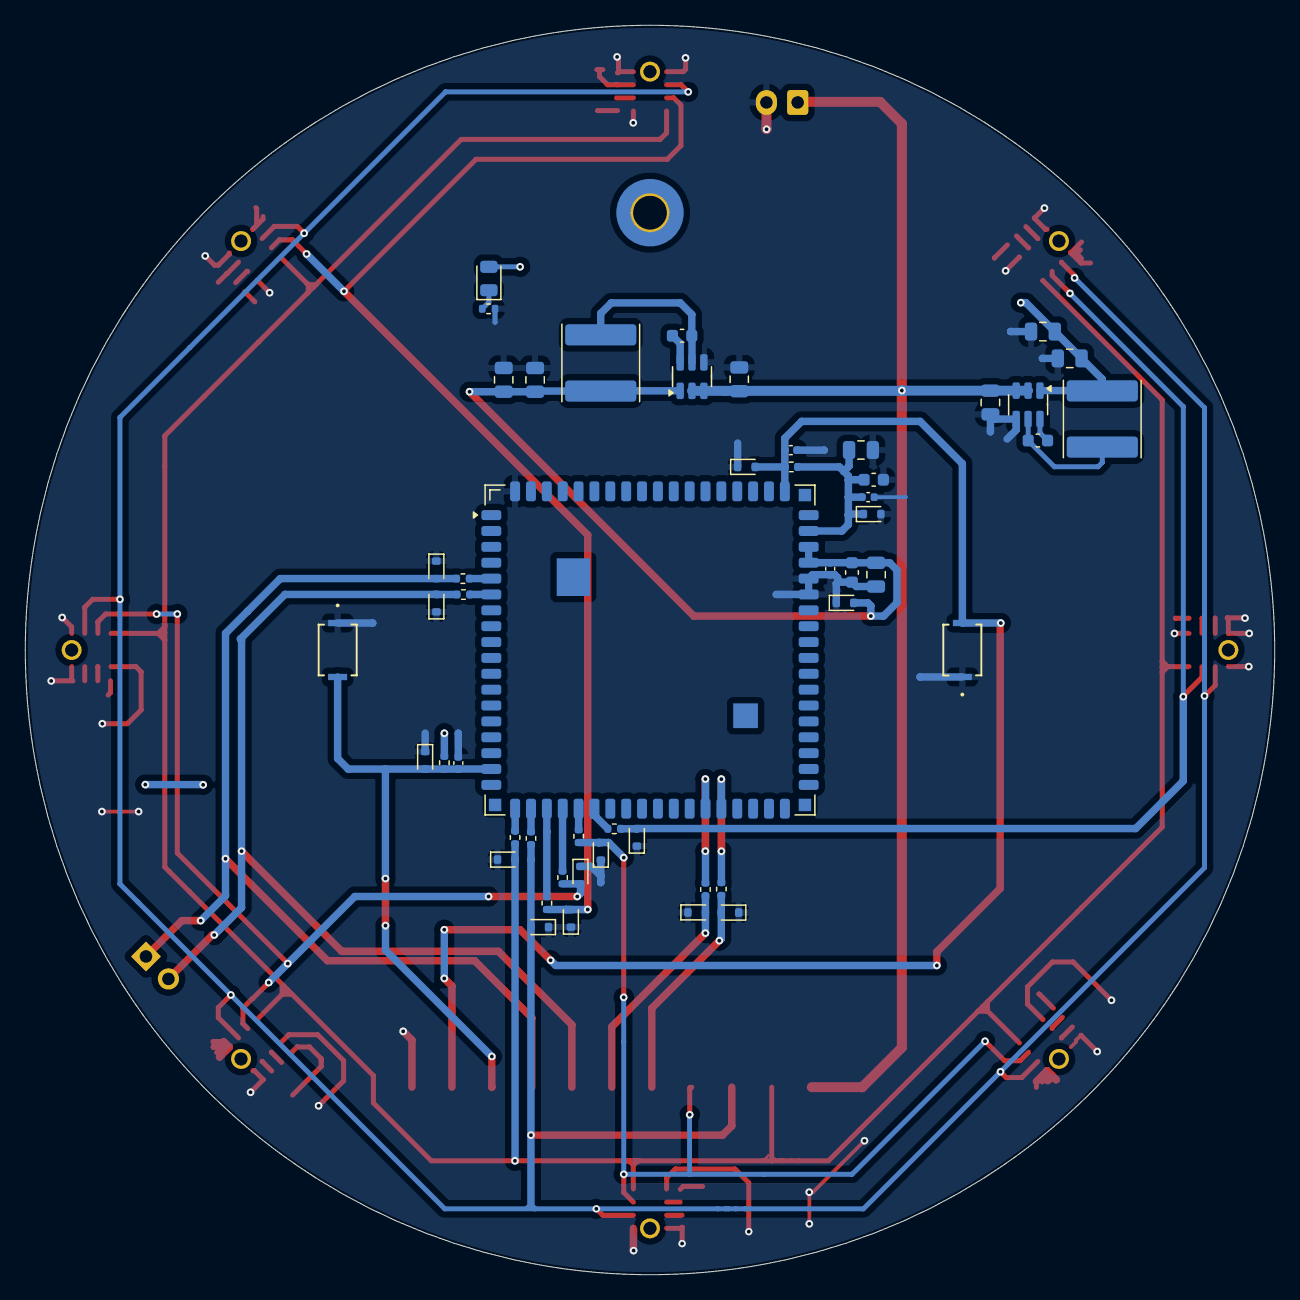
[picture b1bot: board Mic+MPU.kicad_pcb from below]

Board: 2 copper layers, 100.0 x 100.0 mm, 79 parts (51 on the bottom side), 40 nets.
